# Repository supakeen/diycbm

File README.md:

# diycbm

This repository has moved to [another git forge](https://src.tty.cat/DIYCBM/TMA).

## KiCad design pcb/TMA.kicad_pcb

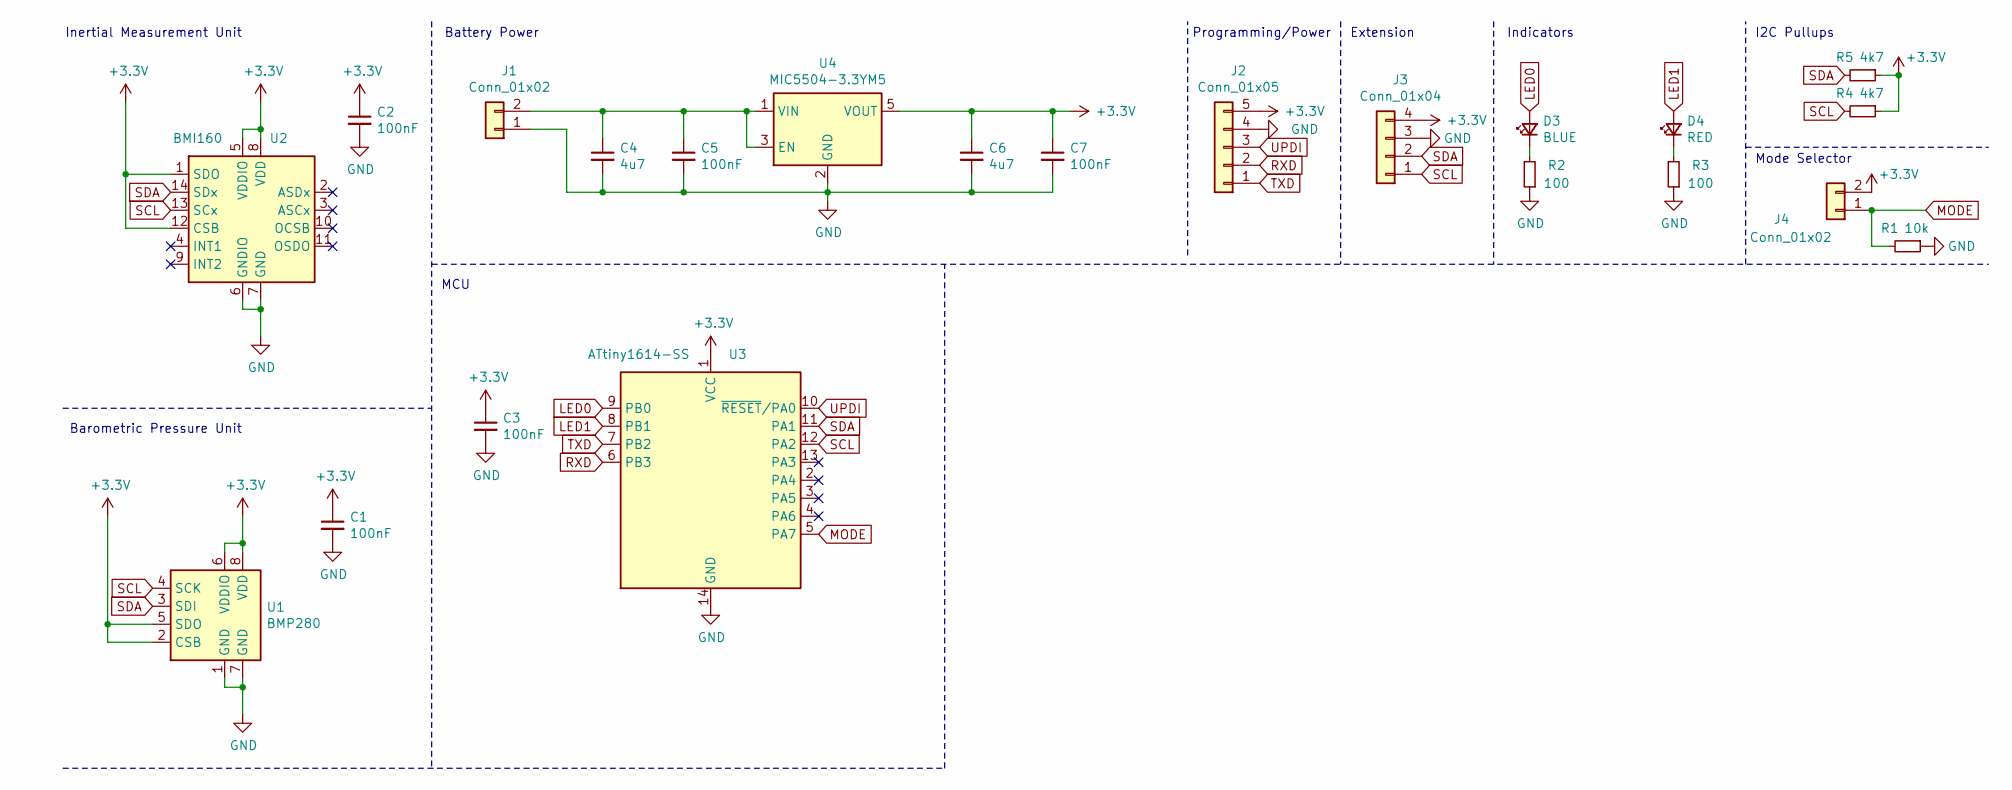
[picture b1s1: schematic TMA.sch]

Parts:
C1, C2, C3, C5, C7: 100nF; C_0402_1005Metric
C4, C6: 4u7; C_0402_1005Metric
D3: BLUE; LED_0402_1005Metric
D4: RED; LED_0402_1005Metric
J1, J4: Conn_01x02; JST_PH_S2B-PH-K_1x02_P2.00mm_Horizontal
J2: Conn_01x05; JST_PH_S5B-PH-K_1x05_P2.00mm_Horizontal
J3: Conn_01x04; JST_PH_S4B-PH-K_1x04_P2.00mm_Horizontal
R1: 10k; R_0402_1005Metric
R2, R3: 100; R_0402_1005Metric
R4, R5: 4k7; R_0402_1005Metric
U1: BMP280; Bosch_LGA-8_2x2.5mm_P0.65mm_ClockwisePinNumbering
U2: BMI160; Bosch_LGA-14_3x2.5mm_P0.5mm
U3: ATtiny1614-SS; SOIC-14_3.9x8.7mm_P1.27mm
U4: MIC5504-3.3YM5; SOT-23-5

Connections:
+3V3: C1.1, C2.1, C3.1, C6.1, C7.1, J2.5, J3.4, J4.2, R4.1, R5.1, U1.2 (CSB), U1.5 (SDO), U1.6 (VDDIO), U1.8 (VDD), U2.1 (SDO), U2.5 (VDDIO), U2.8 (VDD), U2.12 (CSB), U3.1 (VCC), U4.5 (VOUT)
GND: C1.2, C2.2, C3.2, C4.2, C5.2, C6.2, C7.2, J1.1, J2.4, J3.3, R1.1, R2.1, R3.1, U1.1 (GND), U1.7 (GND), U2.6 (GNDIO), U2.7 (GND), U3.14 (GND), U4.2 (GND)
LED0: D3.2 (A), U3.9 (PB0)
LED1: D4.2 (A), U3.8 (PB1)
MODE: J4.1, R1.2, U3.5 (PA7)
unnamed: C4.1, C5.1, J1.2, U4.1 (VIN), U4.3 (EN)
unnamed: D3.1 (K), R2.2
unnamed: D4.1 (K), R3.2
RXD: J2.2, U3.6 (PB3)
SCL: J3.1, R4.2, U1.4 (SCK), U2.13 (SCx), U3.12 (PA2)
SDA: J3.2, R5.2, U1.3 (SDI), U2.14 (SDx), U3.11 (PA1)
TXD: J2.1, U3.7 (PB2)
UPDI: J2.3, U3.10 (~RESET~/PA0)

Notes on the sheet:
Inertial Measurement Unit
Barometric Pressure Unit
MCU
Battery Power
Programming/Power
Indicators
I2C Pullups
Extension
Mode Selector

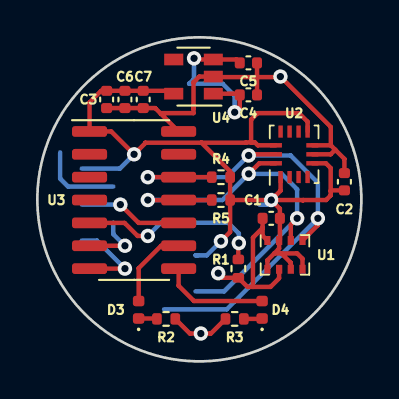
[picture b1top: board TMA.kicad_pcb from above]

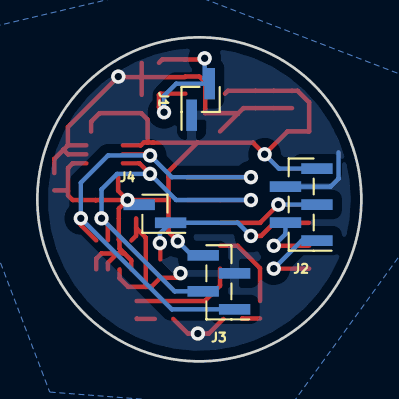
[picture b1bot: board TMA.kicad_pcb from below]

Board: 2 copper layers, 18.0 x 18.0 mm, 22 parts (4 on the bottom side), 13 nets.

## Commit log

2021-04-14 Initial.
2021-04-14 Add a README.
2021-04-14 Add pullups and mode switch, closes #1 and #2.
2021-04-14 Connect MODE label and update sheet comments.
2021-04-14 Add plot PDF.
2021-04-14 Remove pull-down for SPDT, update symbols.
2021-04-14 Important alignment issues.
2021-04-15 Rename directory.
2021-04-15 Add link to schema.
2021-04-15 Update schema to have Schottky connected and 3V3 up.
2021-04-15 Remove other Schottky.
2021-04-15 Alignment.
2021-04-15 Pick components.
2021-04-15 Serial, simplify programmer (trust it), break out I2C.
2021-04-15 Update.
2021-04-16 Simplify, add voltage to extension.
2021-04-16 Routing!
2021-04-16 Fix up silkscreen.
2021-04-17 Minor clean up.
2021-04-17 Add examples of the PCB.
2021-04-17 Add screenshots in README.
2021-04-19 fix lipo connection, move R1 to front
2021-04-19 Move silk screen, regenerate gerbers.
2022-04-16 maintenance(rename and move of repo)
2022-07-15 move git forge
